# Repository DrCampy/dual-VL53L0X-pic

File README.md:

Distance sensor using two VL53L0X time of flight sensors.

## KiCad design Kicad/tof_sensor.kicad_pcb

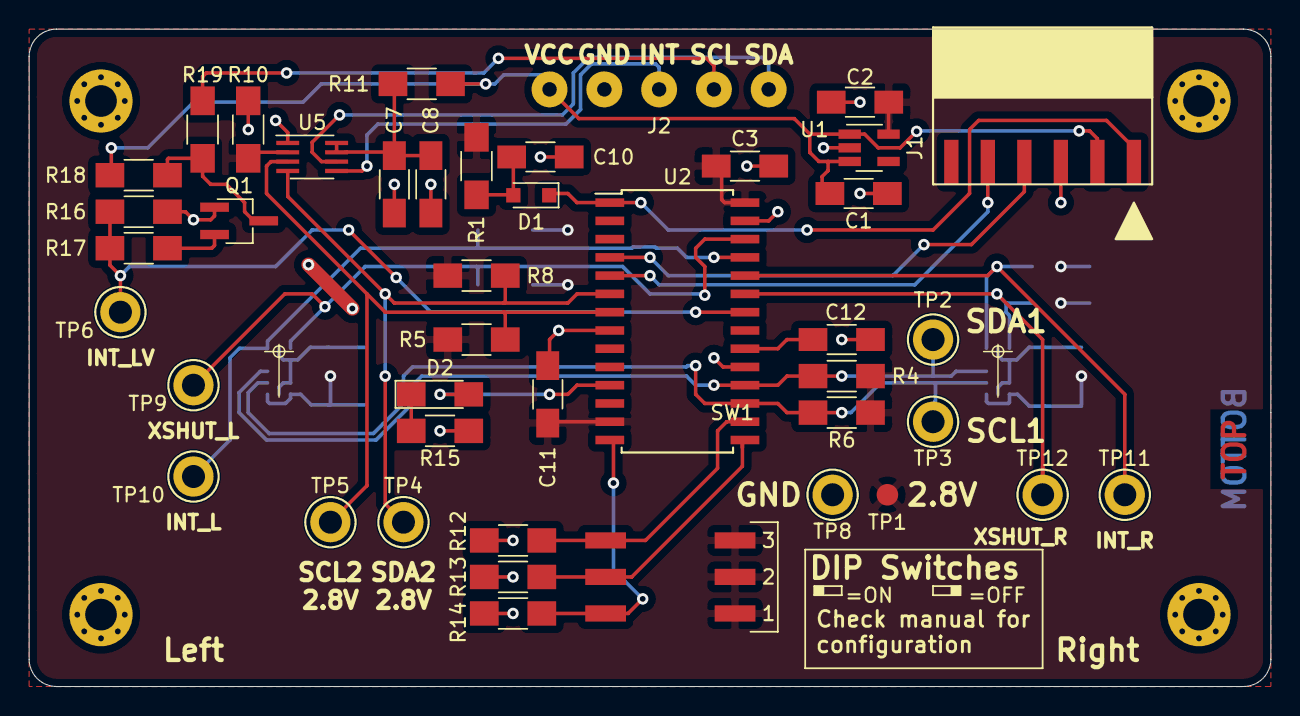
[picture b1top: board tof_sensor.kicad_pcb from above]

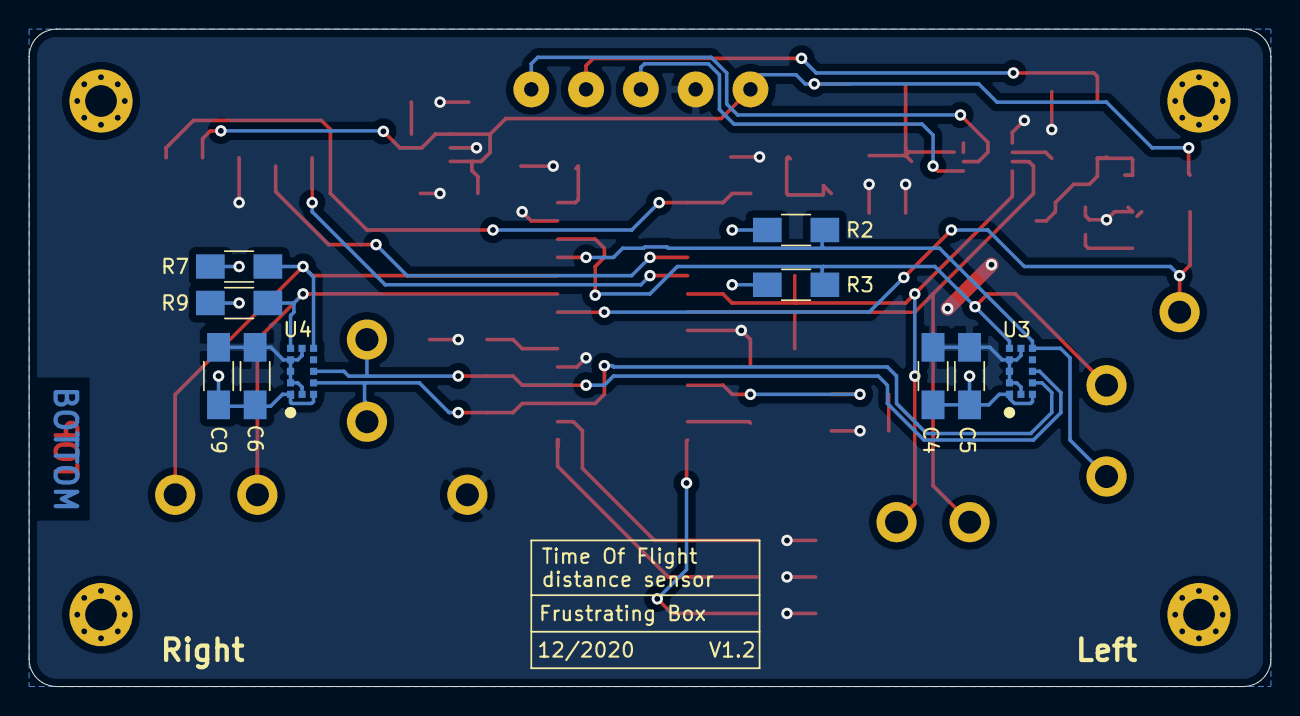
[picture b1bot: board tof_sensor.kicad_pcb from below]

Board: 2 copper layers, 86.4 x 45.7 mm, 53 parts (10 on the bottom side), 28 nets.

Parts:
C1, C2: 1µF; C_1206_HandSoldering
C3, C4, C6, C7, C10, C11: 0.1µF; C_1206_HandSoldering
C5, C8, C9: 4.7µF; C_1206_HandSoldering
C12: 10µF; C_1206_HandSoldering
D1: D_Schottky; D_SOD-323_HandSoldering
D2: LED; LED_1206_HandSoldering
J1: Conn_01x06_Male; Conn_01x06_2.54mm_Horizontal_SMD_Handsoldered
J2: Conn_01x05; SolderWirePad_01x05_2-5mmDrill_HandSoldering
Q1: Q_NMOS_SGD; TSOT-23_HandSoldering
R1, R2, R3, R7, R9, R12, R13, R14, R18: 10kR; R_1206_HandSoldering
R4, R5, R6, R8: 2.2kR; R_1206_HandSoldering
R10: 262.5kR; R_1206_HandSoldering
R11, R16: 200kR; R_1206_HandSoldering
R15: 47R; R_1206_HandSoldering
R17, R19: 330R; R_1206_HandSoldering
SW1: SW_DIP_x03; DIP_Switch_CTS_219_Series_Gull_Wing_HandSoldered
TP1: TestPoint_Probe; Measurement_Point_Round-SMD-Pad_Small
TP2, TP3, TP4, TP5, TP6, TP8, TP9, TP10, TP11, TP12: TestPoint_Probe; Test_Point_Keystone_5010-5014_Multipurpose
U1: MIC5504-2.8YM5; SOT-23-5_HandSoldering
U2: PIC24FJ64GA002; SOIC-28W_7.5x17.9mm_P1.27mm
U3, U4: VL53L0X
U5: PCA9306; SSOP-8_2.95x2.8mm_Pitch0.65mm

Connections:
/DIP1: R14.2, SW1.6, U2.14
/DIP2: R13.2, SW1.5, U2.15
/DIP3: R12.2, SW1.4, U2.16
/ICSPCLK: J1.5, U2.5
/ICSPDAT: J1.4, U2.4
/INT_L: R2.2, TP10.1, U2.25, U3.7
/INT_OUT_VCC: J2.4, R19.2
/INT_OUT_VDD: R16.2, R17.1, TP6.1, U2.22
/INT_R: R7.2, TP11.1, U2.24, U4.7
/LED: D2.2, U2.11
/SCL1: R6.2, TP3.1, U2.17, U3.10, U4.10
/SCL2_HV: J2.5, U5.6
/SCL2_LV: R5.1, TP5.1, U2.7, U5.3
/SDA1: R4.2, TP2.1, U2.18, U3.9, U4.9
/SDA2_HV: J2.3, U5.5
/SDA2_LV: R8.1, TP4.1, U2.6, U5.4
/Vpp: D1.1, J1.1, U2.1
/XSHUT_L: R3.2, TP9.1, U2.26, U3.5
/XSHUT_R: R9.2, TP12.1, U2.23, U4.5
GND: C1.2, C2.1, C3.1, C4.2, C5.2, C6.2, C7.1, C8.1, C9.2, C10.2, C11.1, C12.2, J1.3, J2.2, Q1.1, R10.2, R12.1, R13.1, R14.1, R15.2, R16.1, TP8.1, U1.2, U2.8, U2.19, U2.27, U3.2, U3.3, U3.4, U3.6, U3.12, U4.2, U4.3, U4.4, U4.6, U4.12, U5.1
unnamed: C7.2, C8.2, R11.2, U5.7, U5.8
unnamed: C10.1, D1.2, R1.1
unnamed: C12.1, U2.20
unnamed: D2.1, R15.1
unnamed: Q1.2, R17.2
unnamed: Q1.3, R18.1, R19.1
VCC: C1.1, J1.2, J2.1, R11.1, R18.2, U1.1, U1.3
VDD: C2.2, C3.2, C4.1, C5.1, C6.1, C9.1, C11.2, R1.2, R2.1, R3.1, R4.1, R5.2, R6.1, R7.1, R8.2, R9.1, R10.1, SW1.1, SW1.2, SW1.3, TP1.1, U1.5, U2.13, U2.28, U3.1, U3.11, U4.1, U4.11, U5.2

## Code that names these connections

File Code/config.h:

/* 
 * File:   config.h
 * Author: Morgan Diepart
 *
 * Created on 27 d�cembre 2019, 01:34
 */

#ifndef CONFIG_H
#define	CONFIG_H

#ifdef	__cplusplus
extern "C" {
#endif

/*Main slave I2C address*/
#define PRIM_SLAVE_I2C_ADDR 0x42
    
/*Secondary slave I2C address*/
#define SEC_SLAVE_I2C_ADDR 0x44
    
/*Offset calibration distance in mm*/    
#define OFFSET_CAL_DISTANCE 100
    
/*XTalk calibration distance in mm*/
#define XTALK_CAL_DISTANCE 500

    
/* Defines bit position for used pins */
#define XSHUT_L 15
#define XSHUT_R 12
#define INT_L 14
#define INT_R 13
#define INT_OUT 11

#define DIP1pin RB5
#define DIP2pin RB6
#define DIP3pin RB7
    
/* EEPROM Data addresses */
#define ADD_RSC_R_L     0x00    /*refSPADCount      right low is    0x00 */
#define ADD_RSC_R_H     0x01    /*refSPADCount      right high is   0x01 */
#define ADD_IAS_R       0x02    /*isApertureSPAD    right is        0x02 */
#define ADD_RSC_L_L     0x03    /*refSPADCount      left low is     0x03 */
#define ADD_RSC_L_H     0x04    /*refSPADCount      left high is    0x04 */
#define ADD_IAS_L       0x05    /*isApertureSPAD    left is         0x05 */
#define ADD_OMM_R_L     0x06    /*offsetMicroMeter  right low is    0x06 */
#define ADD_OMM_R_H     0x07    /*offsetMicroMeter  right high is   0x07 */
#define ADD_OMM_L_L     0x08    /*offsetMicroMeter  left low is     0x08 */
#define ADD_OMM_L_H     0x09    /*offsetMicroMeter  left high is    0x09 */
#define ADD_XTCRMC_R_L  0x0A    /*xTalkCompensationRateMegaCps  right low is    0x0A */
#define ADD_XTCRMC_R_H  0x0B    /*xTalkCompensationRateMegaCps  right high is   0x0B */
#define ADD_XTCRMC_L_L  0x0C    /*xTalkCompensationRateMegaCps  left low is     0x0C */
#define ADD_XTCRMC_L_H  0x0D    /*xTalkCompensationRateMegaCps  left high is    0x0D */
#define ADD_I2C_ADD     0x0E    /*Slave I2C address is 0x0E*/ 
   
#ifdef	__cplusplus
}
#endif

#endif	/* CONFIG_H */

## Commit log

2019-11-07 Importing Project
2019-11-07 Updated schematic
2019-11-07 Writing some specs for expected external I2C registers
2019-11-17 Update file management adding notes creating doxyfile
2019-11-18 Ignoring doc files
2019-11-18 Replacing PIC16F by PIC24F16KL402
2019-11-18 Adding notes
2019-11-19 Adapting the API to PIC architecture [WIP]
2019-11-22 Porting VL53L0X API to PIC24 [WIP]
2019-11-23 Porting API to PIC24 [WIP]
    Should be mostly done. Wait functions must stille be implemented. Heavy optimizations is possible at some places.
2019-11-23 Updating nearly all comments because XC16 is stupid
2019-11-23 Bug fixes
2019-11-23 Updating folders structure
2019-11-24 General optimizations and debug
2019-11-25 Changing PIC on schematic
2019-11-25 Updating code to fit new pic
    new pic is PIC24FJ64GA702
2019-11-29 Implementing code [WIP]
2019-12-04 Updating schematic
    Updating PIC layout, re-arranging some signals, adding an int_out line to trigger interrupt for external master.
    Adding DIP switches for configuration
2019-12-04 Updating pin associated macros
2019-12-04 Slave I2C interrupt
2019-12-04 Fixed typo
2019-12-04 Writing sensors configuration code
2019-12-04 updated notes
2019-12-05 Updated Schematic [WIP]
    Added LED
    Associated components and footprints [WIP]
2019-12-05 New notes
2019-12-05 firmware [WIP]
2019-12-06 Footprints [WIP]
2019-12-07 PCB Drawing [WIP]
    Mostly done. A few details remaining
2019-12-08 Updated PCB
    Moved sensors closer to one another
    Reduced size of PCB
2019-12-08 Drawing pictures and schematics
2019-12-13 Improving PCB Design
2019-12-14 Removed old library
2019-12-14 Interrupt Drive
    Adding an interrupt drive so it is compatible with VCC levels
2019-12-14 Renamed PIC
2019-12-14 Updated PCB
    Added int drive
    Added informative text
2019-12-15 Ignoring fab files
2019-12-15 Updated PCB text
2019-12-16 Updated some pictures
2019-12-27 Edited JLC reference text
2019-12-27 Added GPL logo
2020-01-11 Added EEPROM emulation library
2020-01-12 Firmware [WIP]
    beginning implementation of slave I2C
2020-01-12 Removing bad include directive
2020-02-04 Slave i2c (firmware) [WIP]
2020-02-04 deleted old file
2020-02-07 Slave i2c (firmware) [WIP)
2020-02-14 I2C Slave (firmware) [WIP]
2020-02-15 Added functions to make possible saving I2C slave address
2020-02-16 Updated PCB 3D models
2020-02-16 Added 3d renderings of the circuit
2020-02-16 Change i2c address saving functions
2020-02-16 Update main function
2020-02-16 Slave I2C (firmware)
    Slave I2C is basically finished.
    Needs debug
2020-02-16 Updated specs file
2020-02-16 Remove legal disclaimer from microchip
2020-02-16 New files for sensor specific functions
2020-02-17 Mode emun values collide with defines
2020-02-17 Making sensor global variables
2020-02-17 Xtalk enabling/disabling functions
2020-02-17 Internal state structure [WIP]
2020-02-17 Change applyConfigX to setConfigX
2020-02-17 Update comments
2020-02-17 State is independant variables instead of struct
2020-02-17 Add auto_inc flag
    Still unused
2020-02-18 applyConfig changed to setConfig
2020-02-18 Global variables changes fixing mistakes
2020-02-18 Adding sensor functions [WIP]
2020-02-21 Removed High distance registers
    Only registers with centimeters (integer) was kept.
2020-02-21 Renamed distance variables
2020-02-21 Update I2C Slave
2020-02-21 Config Update function
2020-02-21 Sensors Interrupts
2020-02-21 Main Function [WIP]
2020-02-22 Change distance register addresses
2020-02-22 I2C Slave fixes
    Fixed using old variable instead of global flag.
    Deleted unused functions
2020-02-22 Add interrupts management functions and interrupt init
2020-02-22 Added trigger when dist register read
2020-02-24 Reading distance register resets CONV_FINISHED flag
2020-02-24 General comments and formatting improvements
2020-02-24 Main file written
2020-02-24 Edited comments
2020-02-24 Keyed VL53L0X footprint
2020-02-27 Update I2CSlaveSetAddress
    Function will not change the I2C address used in secondary address mode. It will however change the address programmed for the normal address mode.
2020-02-27 Writing documentation [WIP]
2020-02-27 Moving pictures and pdf files
2020-02-27 Added dual-vl53l0x-sensor.drawio
2020-02-27 Updated dual-vl53l0x-sensor.drawio
2020-02-27 Added dual-vl53l0x-sensor.svg
2020-02-27 Updated .gitignore
2020-02-27 Added dual-vl53l0x-sensor.pdf
2020-02-28 Added annotated-layout.drawio
2020-02-29 Rotated 3D model of dip switch
2020-03-05 Updated value of LED resistor (R15)
2020-03-05 Updated D1 Footprint
    Changed from 1206 to SOD-323
2020-03-06 Updated PCB layout
2020-03-06 Keyed ICSP Header (J1) footprint
2020-03-06 Updated date on PCB
2020-03-06 Changed net ICSP power pin
    Changed from vdd to vcc, power now goes through the 2.8V LDO
2020-03-07 I2C debug + silicon bug
2020-03-07 Disable JTAG
2020-03-07 Misc fixes
2020-03-08 debug [wip]
2020-03-08 X_SHUT and INT swapped
    Were misplaced
2020-03-09 Updated Oscillator configuration code
    Used Microchip MCC generated code
2020-03-09 Debugged I2C writing function
    Just remember to switch analog function of SDA pin to OFF...
2020-03-09 More I2C debug
2020-03-09 USE_I2C_2V8 have to be defined at compilation level
2020-03-09 VL53L0X related debug
    VL53L0X was not properly allocated.
2020-03-09 VL53L0X SetAddress changes address on device
2020-03-10 Clock is now half the frequency
2020-03-10 I2C functions use 8 bits status instead of 32 bits
2020-03-10 Changed i2c VL53L0X_write_byte to define
    hoping to reduce the stack
2020-03-10 Disabled Brown Out Reset
2020-03-10 OSB2 pin is general purpose output
2020-03-12 Changed i2c file name
2020-03-13 I2C do not use interrupts anymore
2020-03-14 I2C1 Debug [Finished]
    I2C1 between pic and sensors now works as expected
2020-03-14 Rearranged some interrupt code
    Created interrupt configuration function in system.c
    I2C2 Init function now enables I2C2 interrupts by itself
2020-03-19 Small tweaks and fixes
2020-03-19 Now it works
2020-03-20 Fixed distance calculation bug
2020-03-20 Switched I2C1 to 400kHz
2020-03-20 Enabled Brown Out Reset
2020-03-20 Changed the internal frequency from 16MHz to 32MHz
2020-03-20 Removed old debug statements
2020-03-20 Restructured code. Now includes MPLAB X project
2020-03-20 Modified gitignore files
2020-03-20 Remove build files
2020-03-20 Remove diverse files created at compile time
2020-03-20 Update .gitignore for code
2020-03-20 Removed dist files
2020-03-20 Use debugger ICD3
2020-03-21 Updated gitignore
2020-03-21 Changed P-MOS by N-MOS for int circuit.
2020-03-21 Updated testpoints
2020-03-21 Replaced mounting holes that went missing
2020-03-21 Removed JLCJLCJLCJLC text label
2020-03-22 Deleted old picture files
2020-03-22 Added new 3d renderings
2020-03-22 Added annotated-layout-front.drawio
2020-03-22 Added annotated-layout-back.drawio
2020-03-22 Updated illustrations
2020-03-22 Updated components reference
2020-03-22 Updated layout section
2020-03-22 created register section [WIP]
2020-03-22 Updated todo
2020-04-02 Moved files
2020-04-02 Added pictures
2020-04-02 Updated layout
2020-04-02 Updated bill of material
2020-04-02 Updated description tex file
2020-04-02 updated registers tex file
2020-04-02 Added title tex file
2020-04-02 added interfaces tex file
2020-04-02 added boot_conf tex file
2020-04-02 added errors tex file
2020-04-02 updated main tex file
2020-04-02 Updated doc todo list
2020-04-02 Updated circuit schematic
2020-04-02 Updated documentation
2020-04-02 deleted todo
2020-04-02 Updated I2C2 interrupt to respond asap with data
2020-04-02 Added datasheet PDF
2020-04-02 Deleted old txt file
2020-04-02 Using union and structures for registers
    Using unions and structs instead of individual bool values
2020-04-02 Updated error codes
2020-04-02 Updated LoadCal
    perform ref calibration at the good time
2020-04-03 Update the measured value only if measurement status is valid
2020-04-03 Fixed I2C slave not acking properly it's address
2020-04-03 Added attributes to remove "unused variable" error at compile time
2020-04-03 Bugfix: reversed union bitfield order
    Bitfield order was incorrect
2020-04-03 Removed old comments
2020-04-03 Removed powerOnSensor / powerOffSensor functions
2020-04-03 Created updateDuration function
    Functions automatically manages the measurement profile we should use given the timing the user allows
2020-04-03 Minor corrections
2020-04-03 Bugfix
    Right sensor was not woken up at initialization causing error 2.
2020-04-03 Updated kicad schematic annotations
2020-04-03 Updated documentation's gitignore
2020-04-03 Updated datasheet
2020-04-03 Updated datasheet
    Rev. A
2020-04-03 Updated project readme
2020-04-03 Renamed sensor 3d renderings
2020-04-03 Fixed long-range parameters
2020-04-04 Updated datasheet
    Added chapter for measurement modes
2020-04-04 Fixed measurement not updated properly
    Measurements were not updated properly if one or both sensors were disabled
2020-04-28 Updated datasheet to Rev. C
    Fixed typos. Specified startup time .
2020-04-28 Removed old commented code
2020-04-28 Using optimisation level 1
2020-05-12 Created KiCad symbol for the sensor
2020-12-17 Updated board files for connector pinout
    Updated connector pinout so that reversing the connector would not create bad reverse polarity connection on the power supply of the board
2021-03-09 Switched to electrohype library
